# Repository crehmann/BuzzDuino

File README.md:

# BuzzDuino
Buzz Wire Game with Adrduino Nano.

## PCB Design & Schematics
The PCB KiCAD files and Gerber files can be found in the KiCad_PCB_Files folder of this repository.

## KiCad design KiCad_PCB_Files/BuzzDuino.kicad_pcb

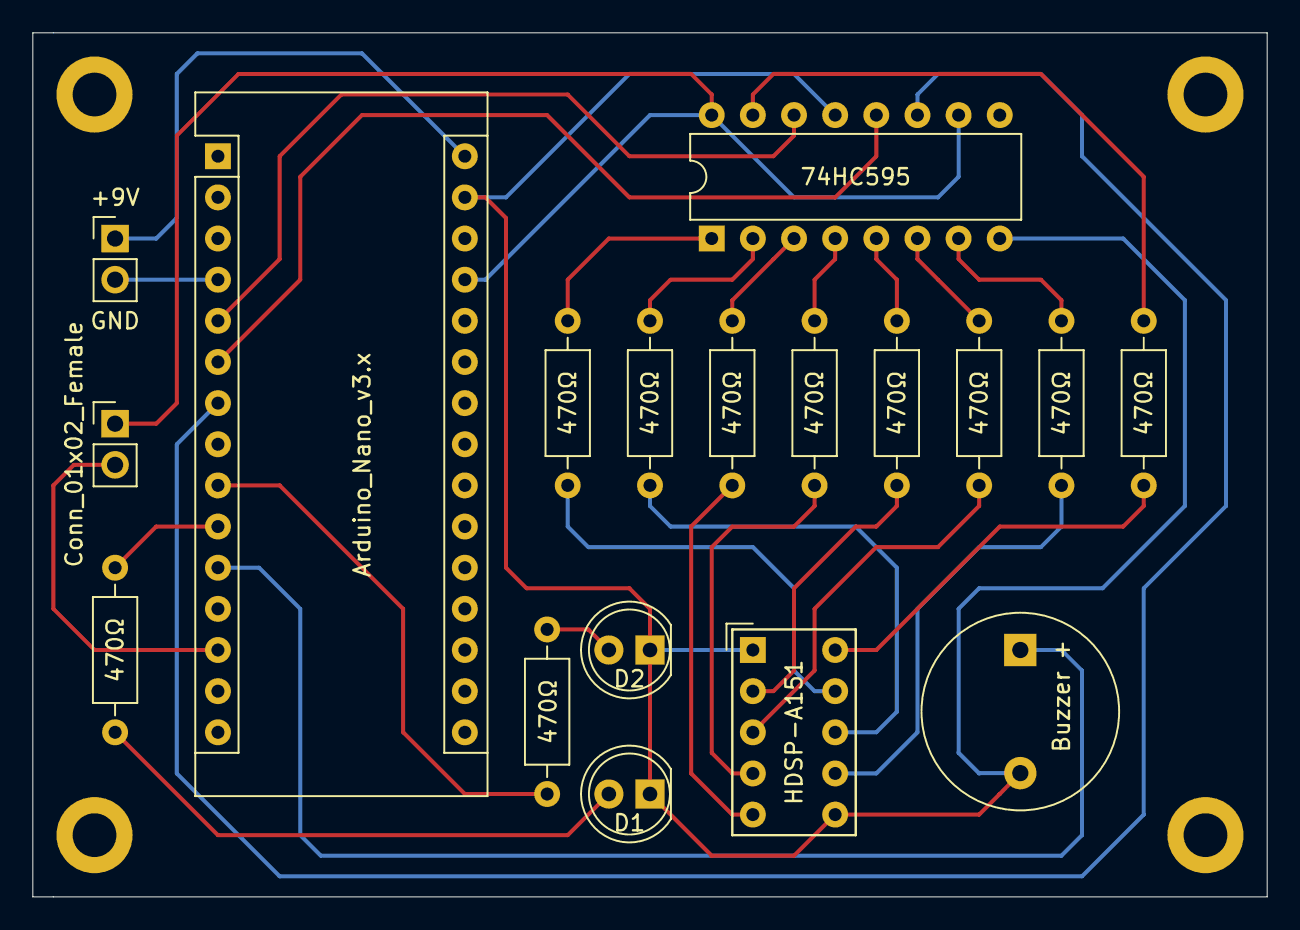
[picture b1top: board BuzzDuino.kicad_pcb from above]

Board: 2 copper layers, 76.2 x 53.3 mm, 18 parts (0 on the bottom side), 29 nets.

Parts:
A1: Arduino_Nano_v3.x; Arduino_Nano
BZ1: Buzzer; Buzzer_12x9.5RM7.6
D1: LED (green); LED_D5.0mm
D2: LED (red); LED_D5.0mm
J1, J2: Conn_01x02_Female; PinHeader_1x02_P2.54mm_Vertical
R1, R2, R3, R4, R5, R6, R7, R8, R9, R10: 470Ω; R_Axial_DIN0207_L6.3mm_D2.5mm_P10.16mm_Horizontal
U1: 74HC595; DIP-16_W7.62mm
U2: HDSP-A151

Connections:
+9V: A1.30, J1.1
/5V: A1.27, J2.1, U1.10, U1.16
GND: A1.29, BZ1.2, D1.1, D2.1, U1.8, U1.13, U2.1, U2.6
unnamed: A1.4, J1.2
unnamed: A1.5, U1.14
unnamed: A1.6, U1.12
unnamed: A1.7, U1.11
unnamed: A1.9, R10.1
unnamed: A1.10, R9.1
unnamed: A1.11, BZ1.1
unnamed: A1.13, J2.2
unnamed: D1.2, R9.2
unnamed: D2.2, R10.2
unnamed: R1.1, U2.10
unnamed: R1.2, U1.15
unnamed: R2.1, U2.9
unnamed: R2.2, U1.1
unnamed: R3.1, U2.8
unnamed: R3.2, U1.2
unnamed: R4.1, U2.5
unnamed: R4.2, U1.3
unnamed: R5.1, U2.4
unnamed: R5.2, U1.4
unnamed: R6.1, U2.2
unnamed: R6.2, U1.5
unnamed: R7.1, U2.3
unnamed: R7.2, U1.6
unnamed: R8.1, U2.7
unnamed: R8.2, U1.7

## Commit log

2020-04-04 added assets
2020-04-04 added KiCad files
2020-04-04 use correct IC pins
2020-04-05 using plated mounting holes
